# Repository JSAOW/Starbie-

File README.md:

# Starbie-

This is an adaptation of the regular starter project "starbie" for Hackclub, Half-Life.
I added an extra button for more controls, a terminal, and battery connections so you can attach a battery to the board and make it portable. 
The right controls map to the same buttons, with the top button bound the same as the right, and I added a square trail because I ran out of time on this project to do much more (along with me not knowing C++ very well). 
I did not add keycaps as I personally like the switches without the keycaps, but if you want, feel free to add them. 
If I were to do this agan, I would probably add more functionality through the code such as adding a new menu with the extras button instead of having two buttons do the same thing (I dont know how to code that well) and add more art/customise it more.

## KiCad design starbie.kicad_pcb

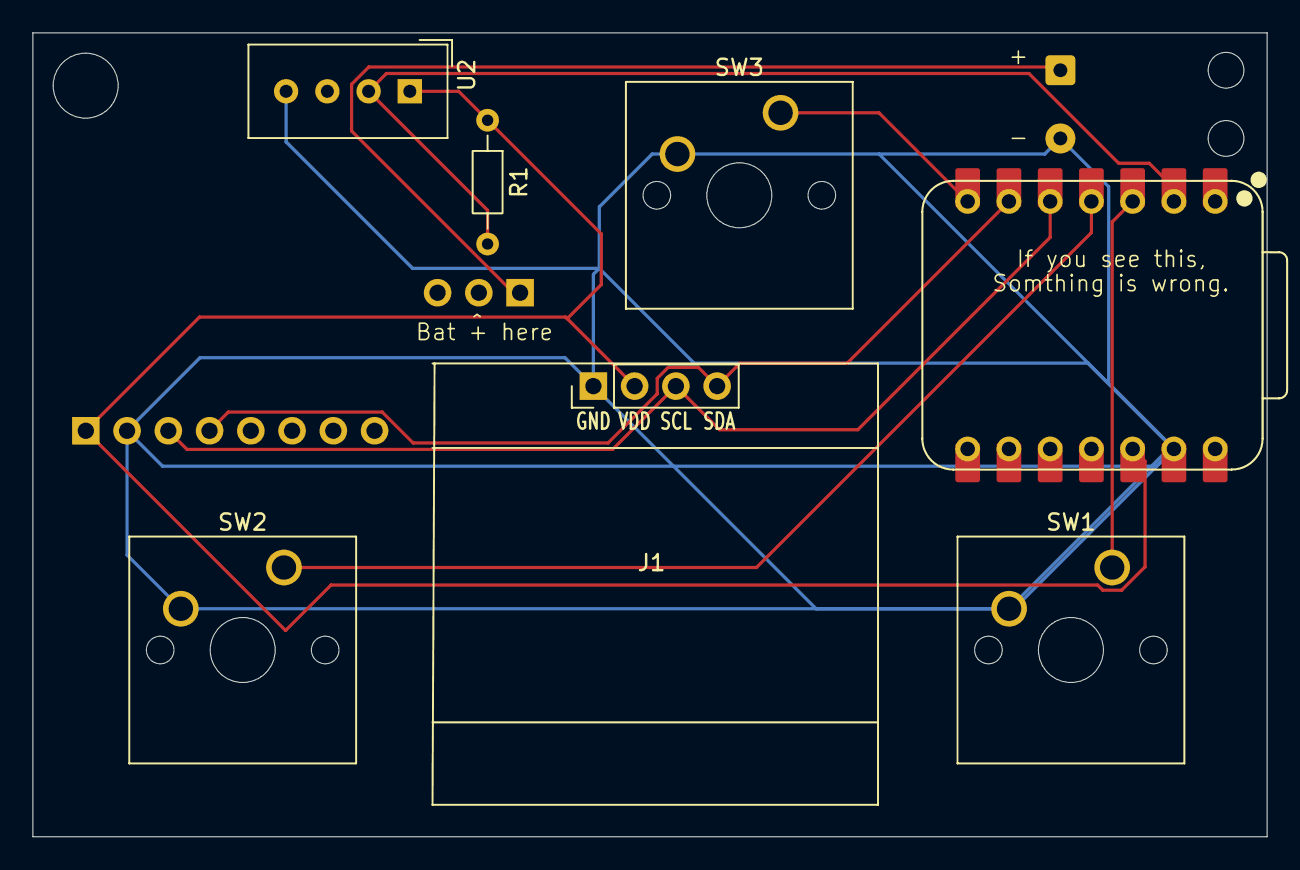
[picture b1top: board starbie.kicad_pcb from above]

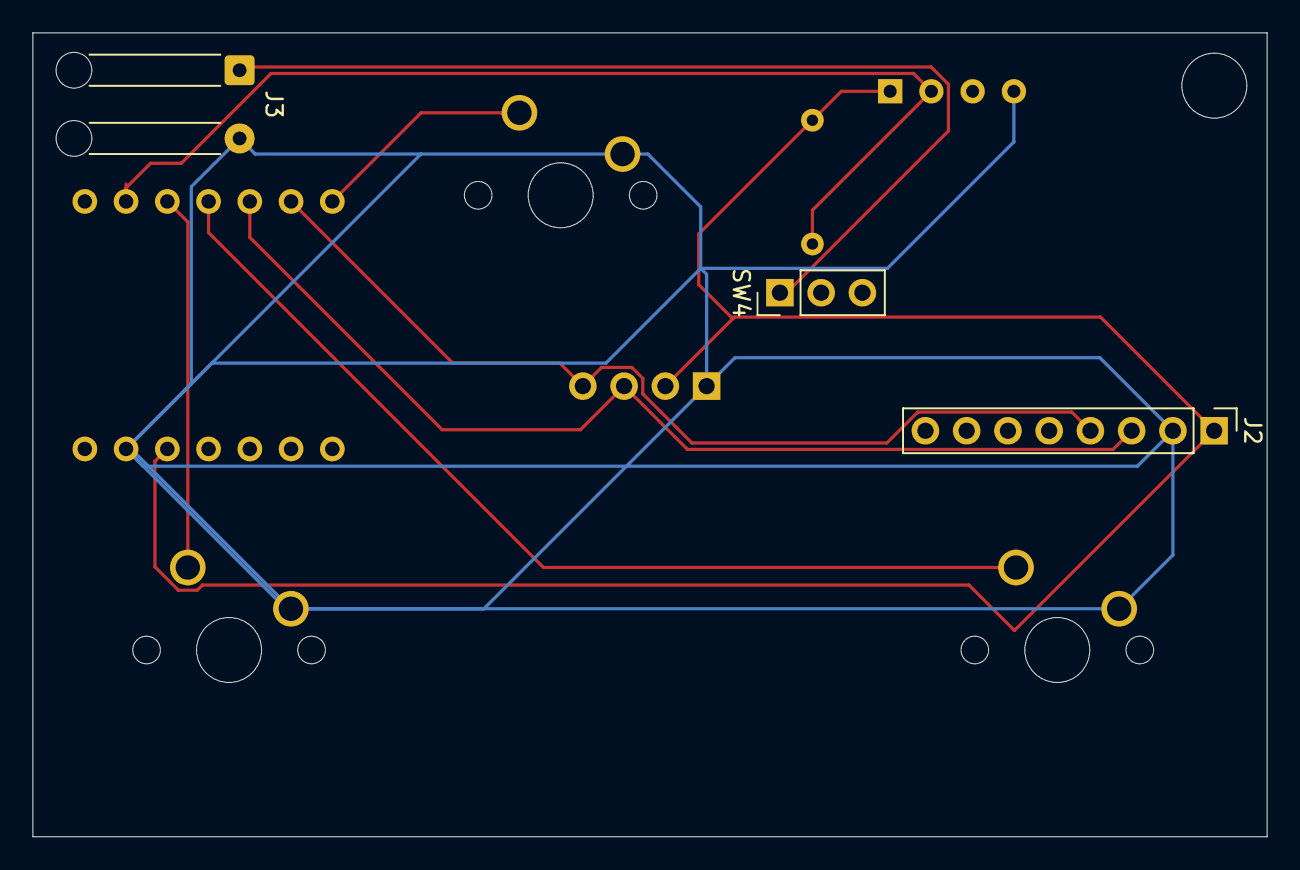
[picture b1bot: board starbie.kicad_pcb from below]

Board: 2 copper layers, 76.0 x 49.5 mm, 10 parts (3 on the bottom side), 9 nets.

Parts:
J1: Conn_01x04_Pin; Display_128x64_096_I2C
J2: Conn_01x08_Pin; PinHeader_1x08_P2.54mm_Vertical
J3: Conn_01x02; SolderWire-0.25sqmm_1x02_P4.2mm_D0.65mm_OD1.7mm_Relief
R1: 10K; R_Axial_DIN0204_L3.6mm_D1.6mm_P7.62mm_Horizontal
SW1, SW2, SW3: SW_Push; SW_Cherry_MX_1.00u_PCB
SW4: SW_SPDT; PinHeader_1x03_P2.54mm_Vertical
U1: XIAO-ESP32-C3-SMD; XIAO-ESP32-C6-DIP
U2: DHT11; Aosong_DHT11_5.5x12.0_P2.54mm

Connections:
+3.3V: J1.2, J2.1, R1.1, U1.12 (3V3_OUT), U2.1 (VDD)
/DHT11 DATA: R1.2, U1.2 (D1), U2.2 (DATA)
/GPIO2: SW1.1, U1.3 (D2)
/GPIO3: SW2.1, U1.4 (D3)
/GPIO4: SW3.1, U1.7 (D6)
/SCL: J1.3, J2.3, U1.5 (D4)
/SDA: J1.4, J2.4, U1.6 (D5)
GND: J1.1, J2.2, J3.2, SW1.2, SW2.2, SW3.2, U1.13 (GND), U2.4 (GND)
unnamed: J3.1, SW4.1 (A)
